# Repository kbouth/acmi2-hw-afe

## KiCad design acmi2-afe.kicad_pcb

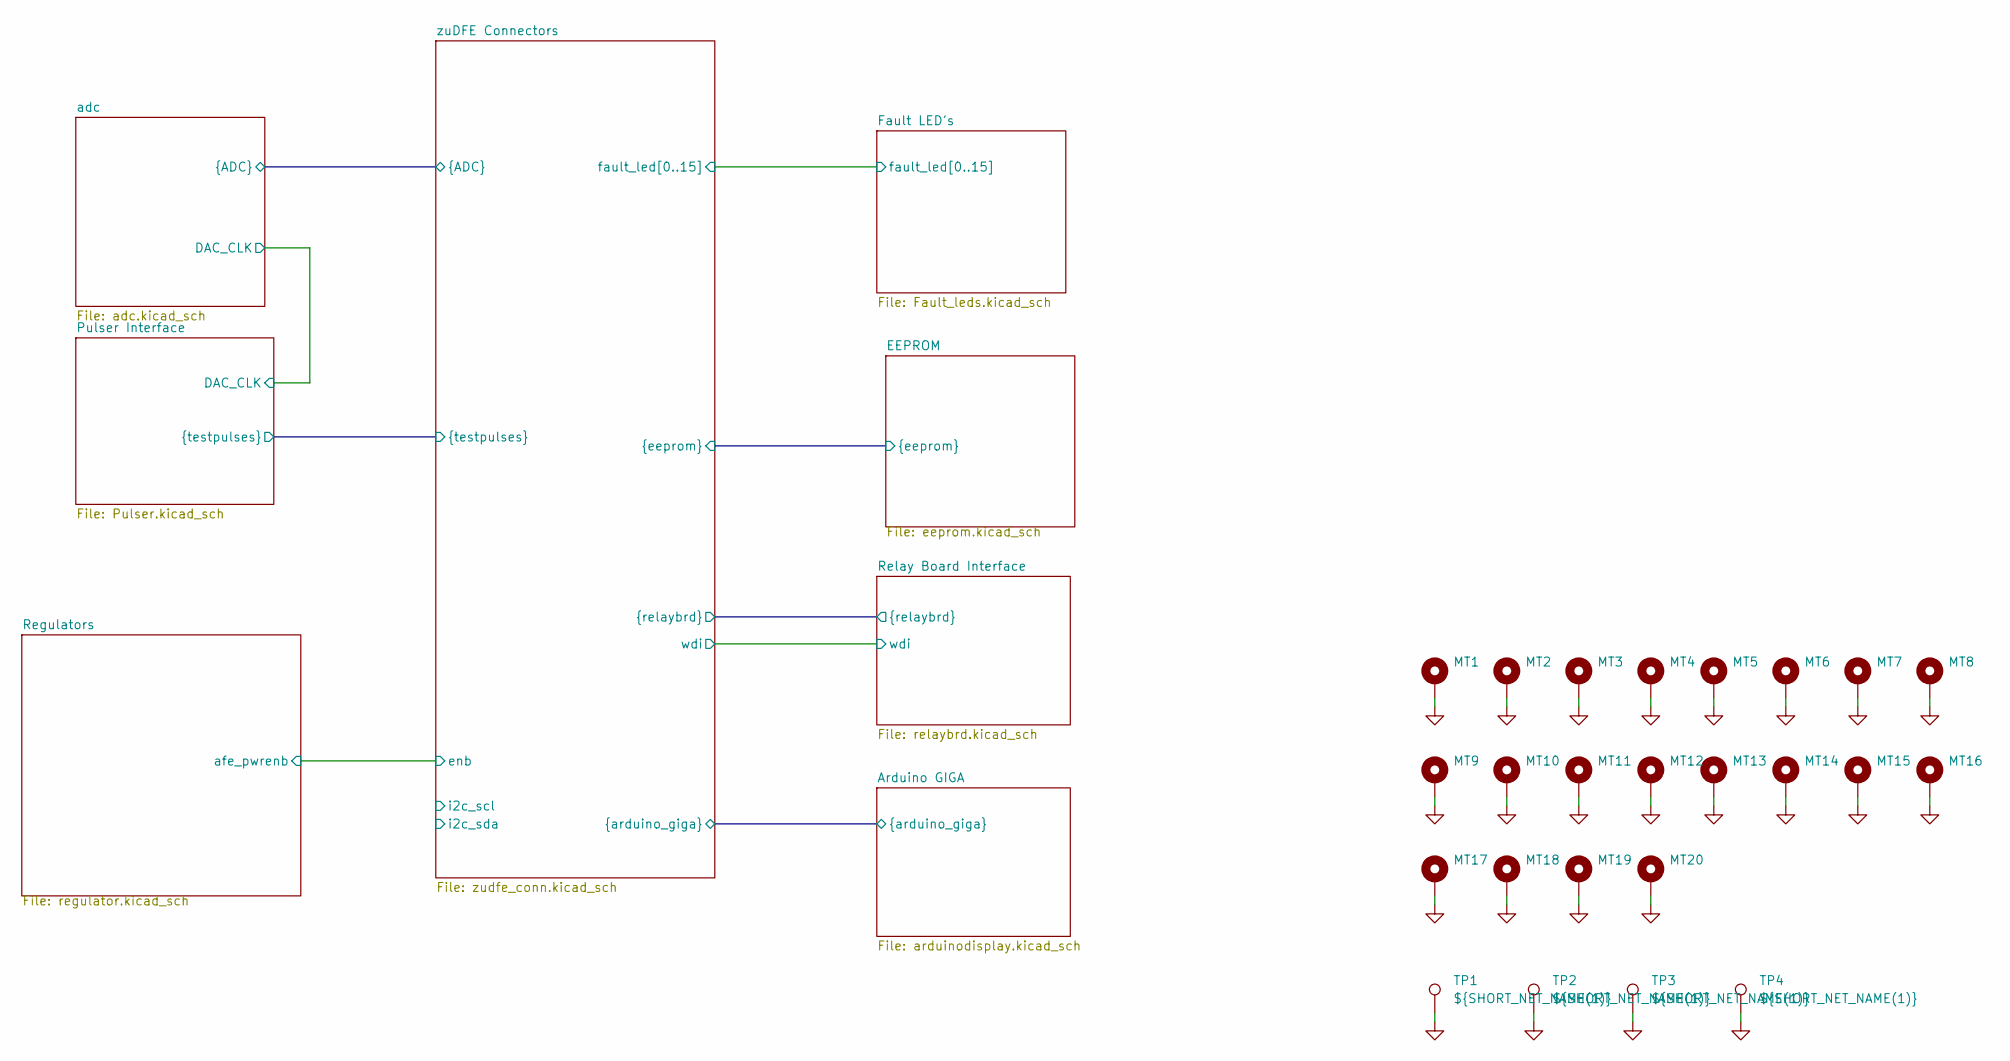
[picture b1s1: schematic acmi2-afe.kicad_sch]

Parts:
MT1, MT2, MT3, MT4, MT5, MT6, MT7, MT8: MountingHole_Pad; MountingHole_4.3mm_M4_DIN965_Pad
MT9, MT10, MT11, MT12, MT13, MT14, MT15, MT16, MT17, MT18, MT19, MT20: MountingHole_Pad; MountingHole_2.2mm_M2_DIN965_Pad
TP1, TP2, TP3, TP4: ${SHORT_NET_NAME(1)}; TestPoint_RCS-0C; MFG_PN RCS-0C

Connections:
GND: MT1.1 (1_1), MT2.1 (1_1), MT3.1 (1_1), MT4.1 (1_1), MT5.1 (1_1), MT6.1 (1_1), MT7.1 (1_1), MT8.1 (1_1), MT9.1 (1_1), MT10.1 (1_1), MT11.1 (1_1), MT12.1 (1_1), MT13.1 (1_1), MT14.1 (1_1), MT15.1 (1_1), MT16.1 (1_1), MT17.1 (1_1), MT18.1 (1_1), MT19.1 (1_1), MT20.1 (1_1), TP1.1 (1_1), TP2.1 (1_1), TP3.1 (1_1), TP4.1 (1_1); also elsewhere on the board

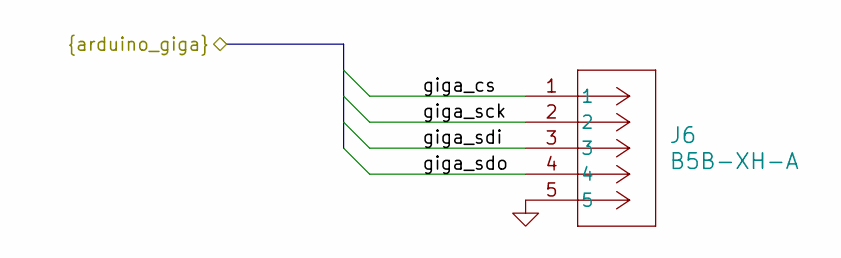
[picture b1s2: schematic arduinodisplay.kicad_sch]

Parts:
J6: B5B-XH-A; CONN_B5B-XH-A_JST

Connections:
/Arduino GIGA/giga_cs: J6.1; also elsewhere on the board
/Arduino GIGA/giga_sck: J6.2; also elsewhere on the board
/Arduino GIGA/giga_sdi: J6.3; also elsewhere on the board
/Arduino GIGA/giga_sdo: J6.4; also elsewhere on the board
GND: J6.5; also elsewhere on the board

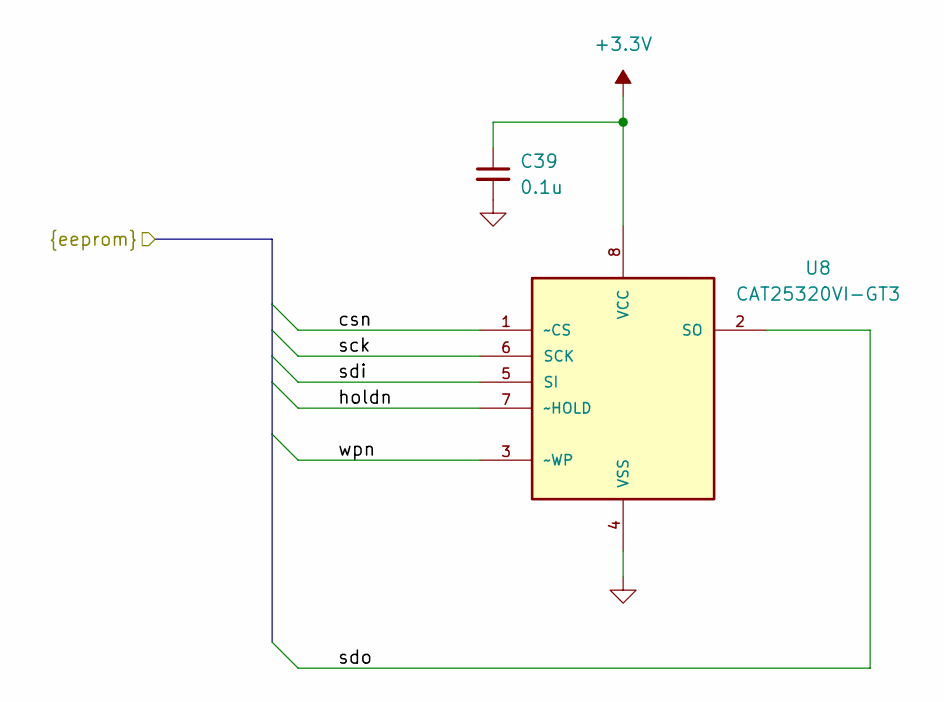
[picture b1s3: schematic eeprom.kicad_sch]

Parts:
C39: 0.1u; C_0805_2012Metric; MFG_PN TMF212B7104KGHT
U8: CAT25320VI-GT3; SOIC127P600X175-8N; MFG_PN CAT25320VI-GT3

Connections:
+3.3V: C39.1, U8.8 (VCC); also elsewhere on the board
/EEPROM/csn: U8.1 (~CS); also elsewhere on the board
/EEPROM/holdn: U8.7 (~HOLD); also elsewhere on the board
/EEPROM/sck: U8.6 (SCK); also elsewhere on the board
/EEPROM/sdi: U8.5 (SI); also elsewhere on the board
/EEPROM/sdo: U8.2 (SO); also elsewhere on the board
/EEPROM/wpn: U8.3 (~WP); also elsewhere on the board
GND: C39.2, U8.4 (VSS); also elsewhere on the board

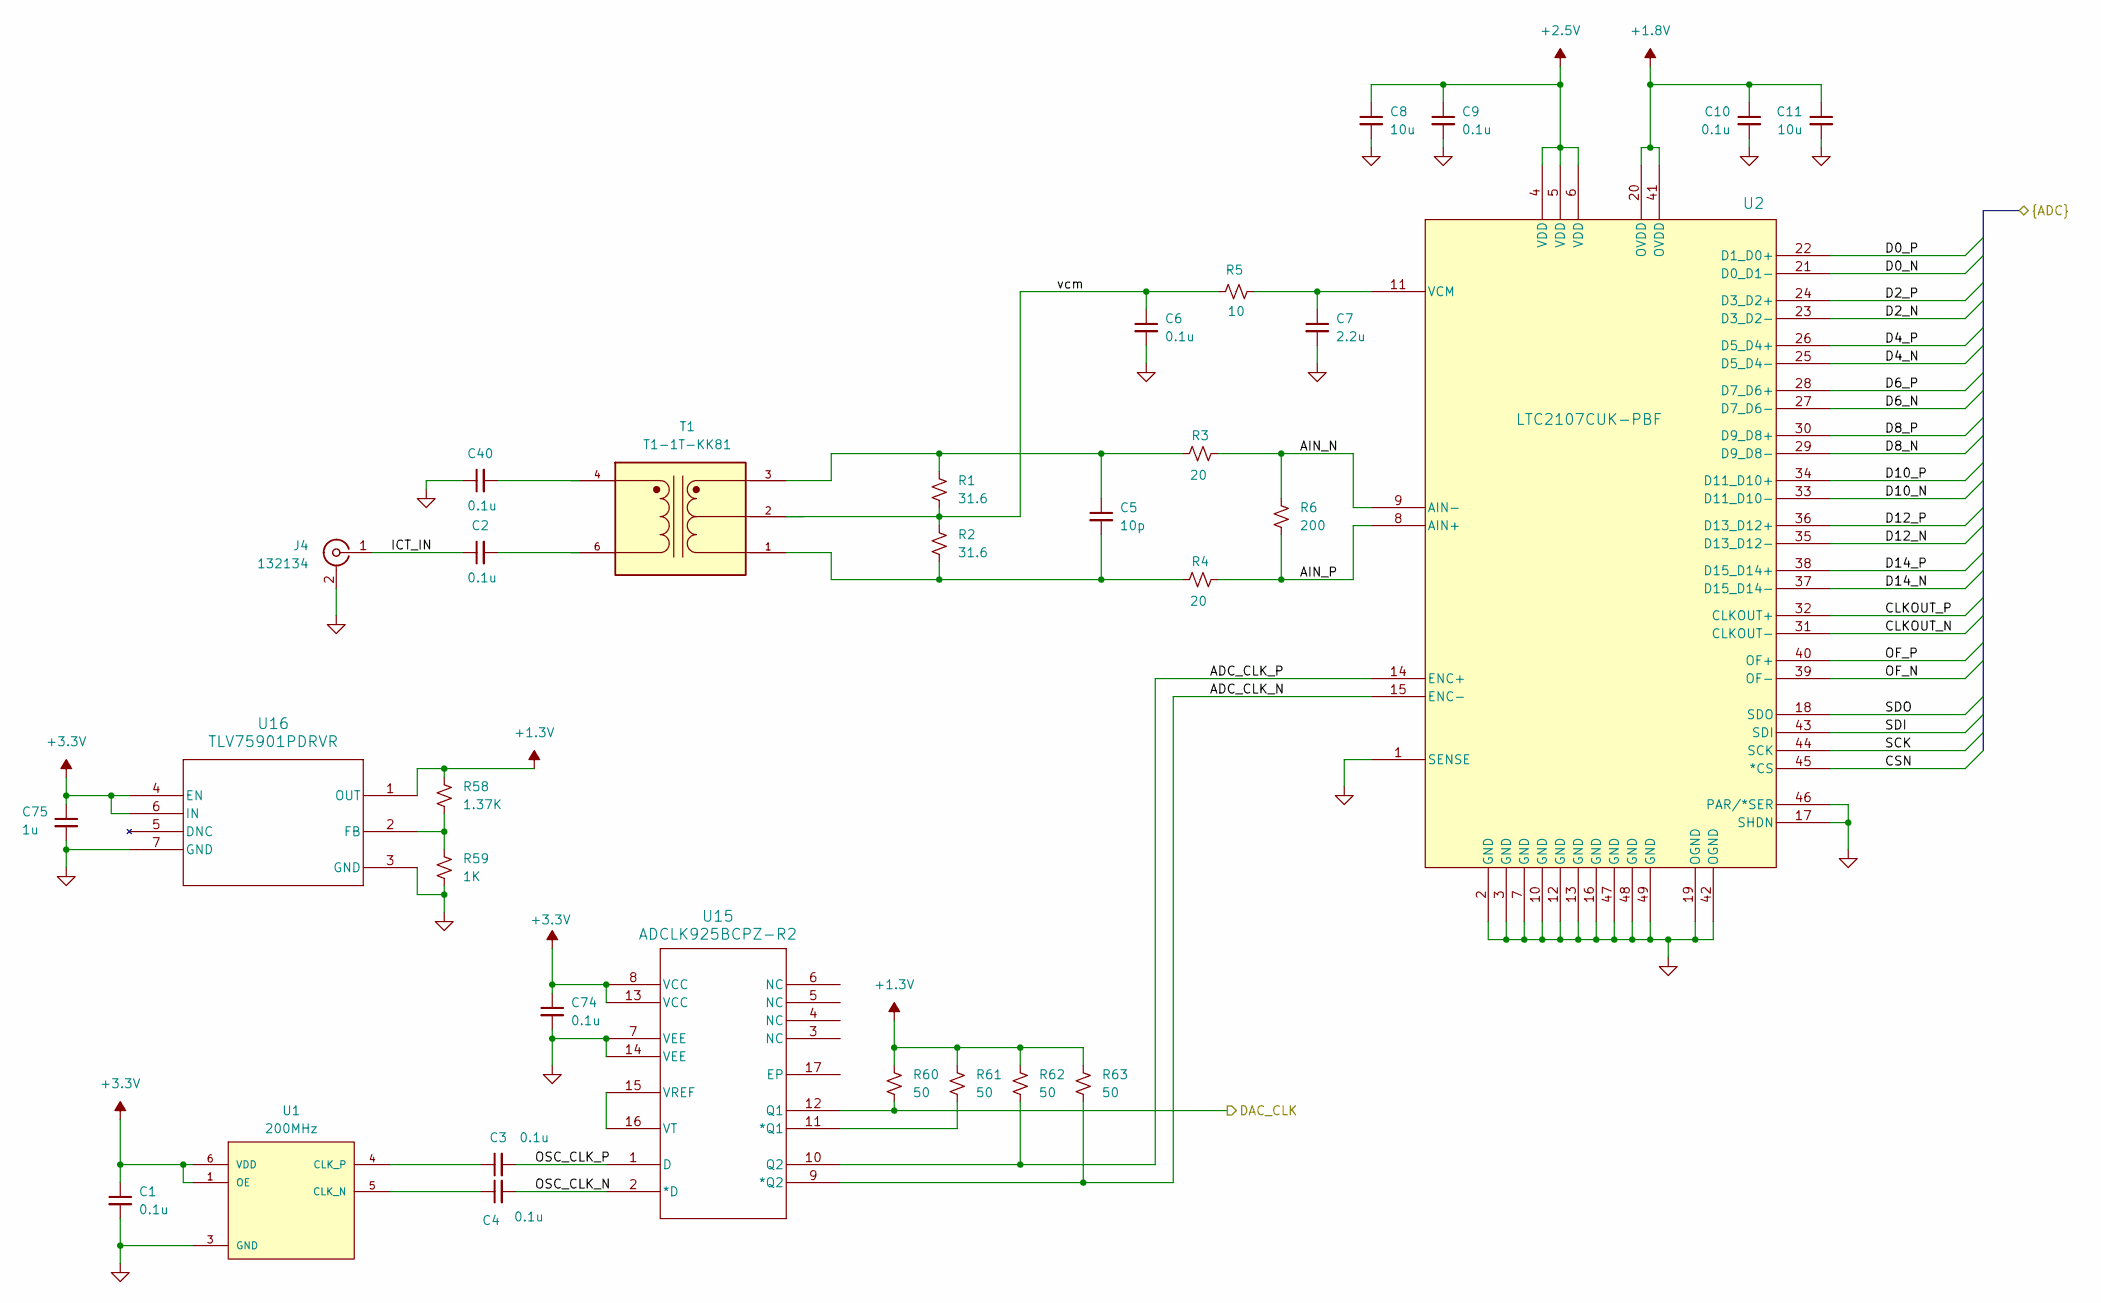
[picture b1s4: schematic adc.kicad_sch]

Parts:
C1, C2, C3, C4, C6, C9, C10, C40, C74: 0.1u; C_0805_2012Metric; MFG_PN TMF212B7104KGHT
C5: 10p; C_0805_2012Metric; MFG_PN QVS212CG100JDHT
C7: 2.2u; C_0805_2012Metric; MFG_PN UMK212BB7225KG-T
C8, C11: 10u; C_0805_2012Metric; MFG_PN GRM21BR61C106KE15K
C75: 1u; C_0805_2012Metric; MFG_PN TMF212B7104KGHT
J4: 132134; SMA_Amphenol_132134_Vertical; MFG_PN 132134
R1, R2: 31.6; R_0805_2012Metric; MFG_PN ERJ-6ENF31R6V
R3, R4: 20; R_0805_2012Metric; MFG_PN ERJ-6ENF20R0V
R5: 10; R_0805_2012Metric; MFG_PN ERJ-6ENF10R0V
R6: 200; R_0805_2012Metric; MFG_PN ERJ-6ENF2000V
R58: 1.37K; R_0805_2012Metric; MFG_PN ERJ-6ENF31R6V
R59: 1K; R_0805_2012Metric; MFG_PN ERJ-6ENF31R6V
R60, R61, R62, R63: 50; R_0805_2012Metric; MFG_PN ERJ-6ENF31R6V
T1: T1-1T-KK81; XFMR_T1-1T-KK81_; PARTREV B
U1: 200MHz; OSC_ECS-LVDS33-2000-BN; MFG_PN ECS-LVDS33-2000-BN
U2: LTC2107CUK-PBF; QFN-48_UK_LIT; MFG_PN LTC2107CUK#PBF
U15: ADCLK925BCPZ-R2; CP_16_3_ADI
U16: TLV75901PDRVR; WSON6_DRV_TEX

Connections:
+1.3V: R58.1, R60.1, R61.1, R62.1, R63.1, U16.1 (OUT)
+1.8V: C10.1, C11.1, U2.20 (OVDD), U2.41 (OVDD); also elsewhere on the board
+2.5V: C8.1, C9.1, U2.4 (VDD), U2.5 (VDD), U2.6 (VDD); also elsewhere on the board
+3.3V: C1.1, C74.1, C75.1, U1.1 (OE), U1.6 (VDD), U15.8 (VCC), U15.13 (VCC), U16.4 (EN), U16.6 (IN); also elsewhere on the board
/Pulser Interface/DAC_CLK: R60.2, U15.12 (Q1); also elsewhere on the board
/adc/ADC_CLK_N: R63.2, U2.15 (ENC-), U15.9 (*Q2)
/adc/ADC_CLK_P: R62.2, U2.14 (ENC+), U15.10 (Q2)
/adc/AIN_N: R3.1, R6.1, U2.9 (AIN-)
/adc/AIN_P: R4.1, R6.2, U2.8 (AIN+)
/adc/CLKOUT_N: U2.31 (CLKOUT-); also elsewhere on the board
/adc/CLKOUT_P: U2.32 (CLKOUT+); also elsewhere on the board
/adc/CSN: U2.45 (*CS); also elsewhere on the board
/adc/D0_N: U2.21 (D0_D1-); also elsewhere on the board
/adc/D0_P: U2.22 (D1_D0+); also elsewhere on the board
/adc/D2_N: U2.23 (D3_D2-); also elsewhere on the board
/adc/D2_P: U2.24 (D3_D2+); also elsewhere on the board
/adc/D4_N: U2.25 (D5_D4-); also elsewhere on the board
/adc/D4_P: U2.26 (D5_D4+); also elsewhere on the board
/adc/D6_N: U2.27 (D7_D6-); also elsewhere on the board
/adc/D6_P: U2.28 (D7_D6+); also elsewhere on the board
/adc/D8_N: U2.29 (D9_D8-); also elsewhere on the board
/adc/D8_P: U2.30 (D9_D8+); also elsewhere on the board
/adc/D10_N: U2.33 (D11_D10-); also elsewhere on the board
/adc/D10_P: U2.34 (D11_D10+); also elsewhere on the board
/adc/D12_N: U2.35 (D13_D12-); also elsewhere on the board
/adc/D12_P: U2.36 (D13_D12+); also elsewhere on the board
/adc/D14_N: U2.37 (D15_D14-); also elsewhere on the board
/adc/D14_P: U2.38 (D15_D14+); also elsewhere on the board
/adc/ICT_IN: C2.1, J4.1 (In)
/adc/OF_N: U2.39 (OF-); also elsewhere on the board
/adc/OF_P: U2.40 (OF+); also elsewhere on the board
/adc/OSC_CLK_N: C4.2, U15.2 (*D)
/adc/OSC_CLK_P: C3.2, U15.1 (D)
/adc/SCK: U2.44 (SCK); also elsewhere on the board
/adc/SDI: U2.43 (SDI); also elsewhere on the board
/adc/SDO: U2.18 (SDO); also elsewhere on the board
/adc/vcm: C6.1, R1.2, R2.1, R5.2, T1.2
GND: C1.2, C6.2, C7.2, C8.2, C9.2, C10.2, C11.2, C40.1, C74.2, C75.2, J4.2 (Ext), R59.2, U1.3 (GND), U2.1 (SENSE), U2.2 (GND), U2.3 (GND), U2.7 (GND), U2.10 (GND), U2.12 (GND), U2.13 (GND), U2.16 (GND), U2.17 (SHDN), U2.19 (OGND), U2.42 (OGND), U2.46 (PAR/*SER), U2.47 (GND), U2.48 (GND), U2.49 (GND), U15.7 (VEE), U15.14 (VEE), U16.3 (GND), U16.7 (GND); also elsewhere on the board
unnamed: C2.2, T1.6
unnamed: C5.1, R1.1, R3.2, T1.3
unnamed: C5.2, R2.2, R4.2, T1.1
unnamed: C40.2, T1.4
unnamed: C4.1, U1.5 (CLK_N)
unnamed: C3.1, U1.4 (CLK_P)
unnamed: C7.1, R5.1, U2.11 (VCM)
unnamed: R61.2, U15.11 (*Q1)
unnamed: U15.15 (VREF), U15.16 (VT)
unnamed: R58.2, R59.1, U16.2 (FB)

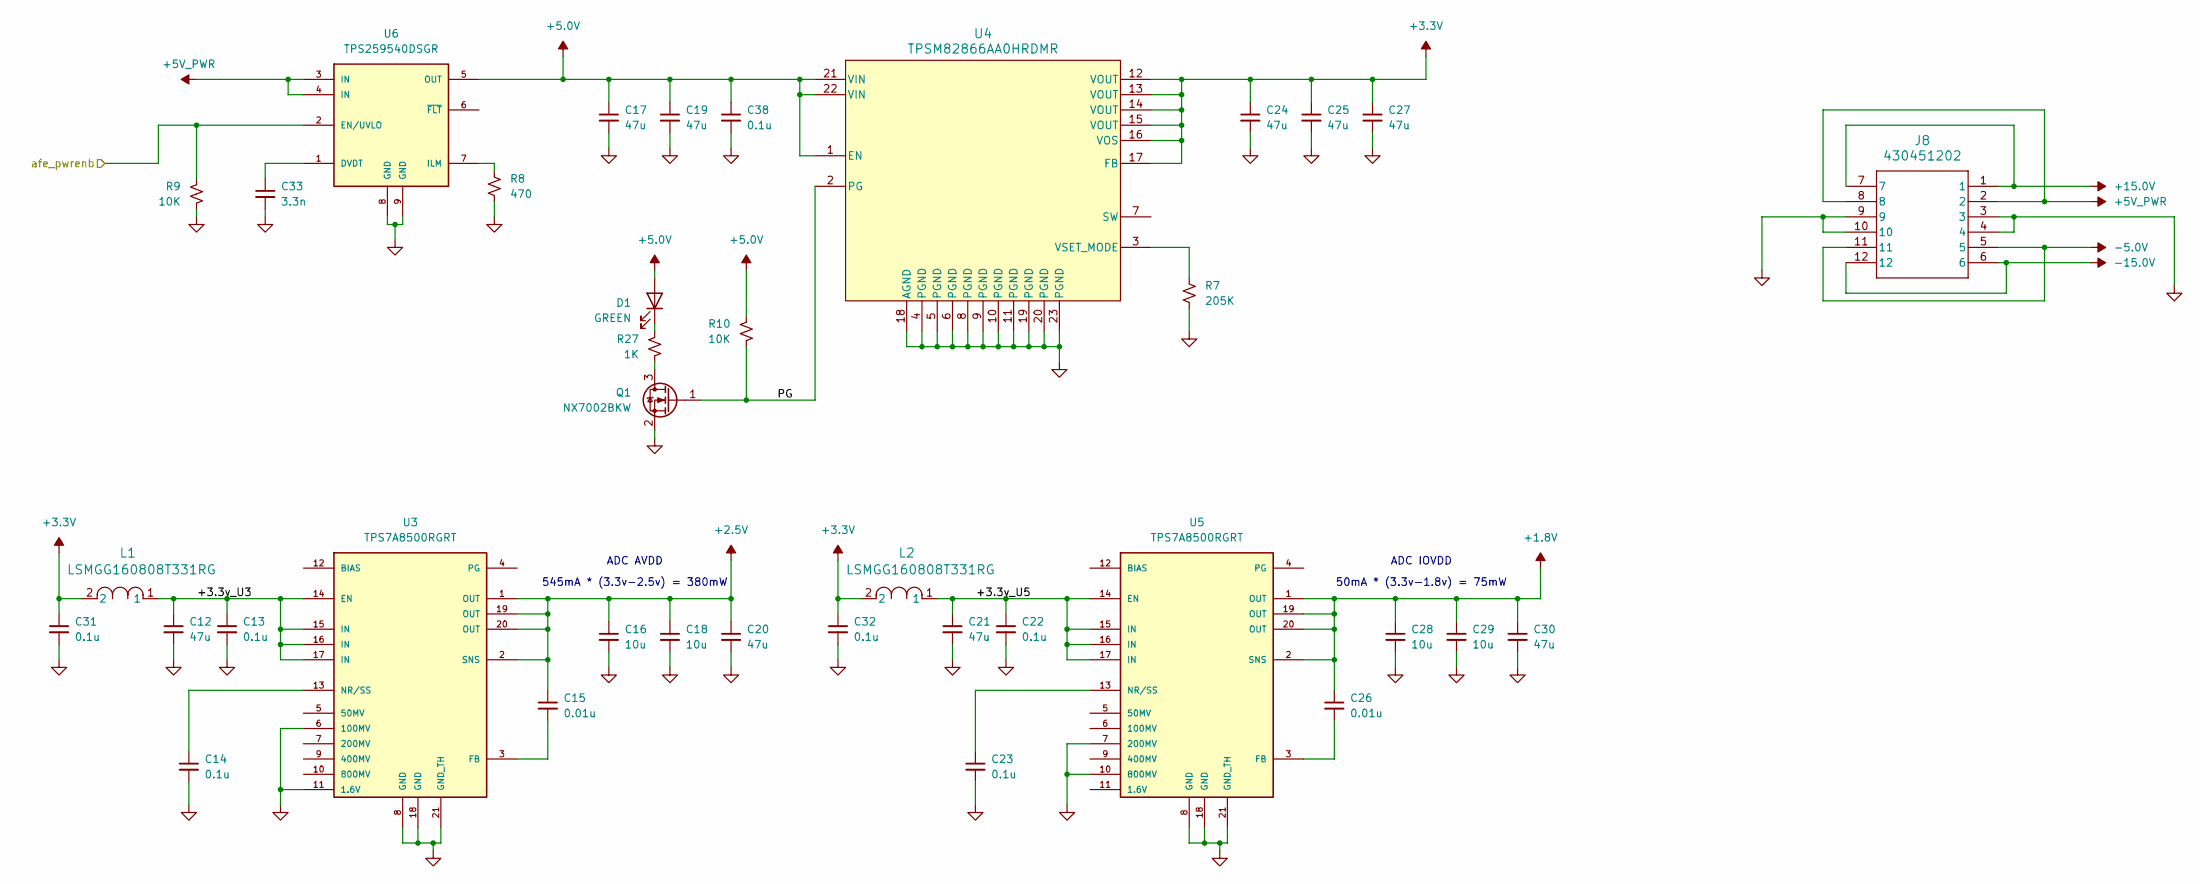
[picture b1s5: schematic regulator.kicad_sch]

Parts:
C12, C17, C19, C20, C21, C24, C25, C27, C30: 47u; C_0805_2012Metric; MFG_PN C2012X5R1A476M125AC
C13, C14, C22, C23, C31, C32, C38: 0.1u; C_0805_2012Metric; MFG_PN TMF212B7104KGHT
C15, C26: 0.01u; C_0805_2012Metric; MFG_PN MAASU21GSL8103MTNA01
C16, C18, C28, C29: 10u; C_0805_2012Metric; MFG_PN GRM21BR61C106KE15K
C33: 3.3n; C_0805_2012Metric; MFG_PN C0805X332K5RECTU
D1: GREEN; LED_0805_2012Metric; MFG_PN LTST-C191KGKT
J8: 430451202; CONN_SD-43045-001_12_MOL
L1, L2: LSMGG160808T331RG; IND_LSMG_160808_TAY; MFG_PN LSMGG160808T331RG
Q1: NX7002BKW; SOT-323_SC-70; MFG_PN NX7002BKWX
R7: 205K; R_0805_2012Metric; MFG_PN ERJ-6ENF2053V
R8: 470; R_0805_2012Metric; MFG_PN ERJ-6ENF4700V
R9, R10: 10K; R_0805_2012Metric; MFG_PN ERJ-2RKF1001X
R27: 1K; R_0805_2012Metric; MFG_PN ERJ-P06F1001V
U3, U5: TPS7A8500RGRT; QFN50P350X350X100-21N; MFG_PN TPS7A8500RGRT
U4: TPSM82866AA0HRDMR; RDM0023A-MFG; MFG_PN TPSM82866AA0HRDMR
U6: TPS259540DSGR; SON50P200X200X80-9N; MFG_PN TPS259540DSGR

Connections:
+1.8V: C26.1, C28.1, C29.1, C30.1, U5.1 (OUT), U5.2 (SNS), U5.19 (OUT), U5.20 (OUT); also elsewhere on the board
+2.5V: C15.1, C16.1, C18.1, C20.1, U3.1 (OUT), U3.2 (SNS), U3.19 (OUT), U3.20 (OUT); also elsewhere on the board
+3.3V: C24.1, C25.1, C27.1, C31.1, C32.1, L1.2, L2.2, U4.12 (VOUT), U4.13 (VOUT), U4.14 (VOUT), U4.15 (VOUT), U4.16 (VOS), U4.17 (FB); also elsewhere on the board
+5.0V: C17.1, C19.1, C38.1, D1.2 (A), R10.1, U4.1 (EN), U4.21 (VIN), U4.22 (VIN), U6.5 (OUT); also elsewhere on the board
+5V_PWR: J8.2, J8.8, U6.3 (IN), U6.4 (IN); also elsewhere on the board
+15.0V: J8.1, J8.7; also elsewhere on the board
-5.0V: J8.5, J8.11; also elsewhere on the board
-15.0V: J8.6, J8.12; also elsewhere on the board
/Regulators/+3.3v_U3: C12.1, C13.1, L1.1, U3.14 (EN), U3.15 (IN), U3.16 (IN), U3.17 (IN)
/Regulators/+3.3v_U5: C21.1, C22.1, L2.1, U5.14 (EN), U5.15 (IN), U5.16 (IN), U5.17 (IN)
/Regulators/PG: Q1.1 (G), R10.2, U4.2 (PG)
/Regulators/afe_pwrenb: R9.1, U6.2 (EN/UVLO); also elsewhere on the board
GND: C12.2, C13.2, C14.2, C16.2, C17.2, C18.2, C19.2, C20.2, C21.2, C22.2, C23.2, C24.2, C25.2, C27.2, C28.2, C29.2, C30.2, C31.2, C32.2, C33.2, C38.2, J8.3, J8.4, J8.9, J8.10, Q1.2 (S), R7.2, R8.2, R9.2, U3.6 (100MV), U3.8 (GND), U3.11 (1.6V), U3.18 (GND), U3.21 (GND_TH), U4.4 (PGND), U4.5 (PGND), U4.6 (PGND), U4.8 (PGND), U4.9 (PGND), U4.10 (PGND), U4.11 (PGND), U4.18 (AGND), U4.19 (PGND), U4.20 (PGND), U4.23 (PGND), U5.7 (200MV), U5.8 (GND), U5.10 (800MV), U5.18 (GND), U5.21 (GND_TH), U6.8 (GND), U6.9 (GND); also elsewhere on the board
unnamed: D1.1 (K), R27.1
unnamed: Q1.3 (D), R27.2
unnamed: C15.2, U3.3 (FB)
unnamed: C14.1, U3.13 (NR/SS)
unnamed: R7.1, U4.3 (VSET_MODE)
unnamed: C26.2, U5.3 (FB)
unnamed: C23.1, U5.13 (NR/SS)
unnamed: C33.1, U6.1 (DVDT)
unnamed: R8.1, U6.7 (ILM)

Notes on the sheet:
50mA * (3.3v-1.8v) = 75mW
ADC IOVDD
ADC AVDD
545mA * (3.3v-2.5v) = 380mW

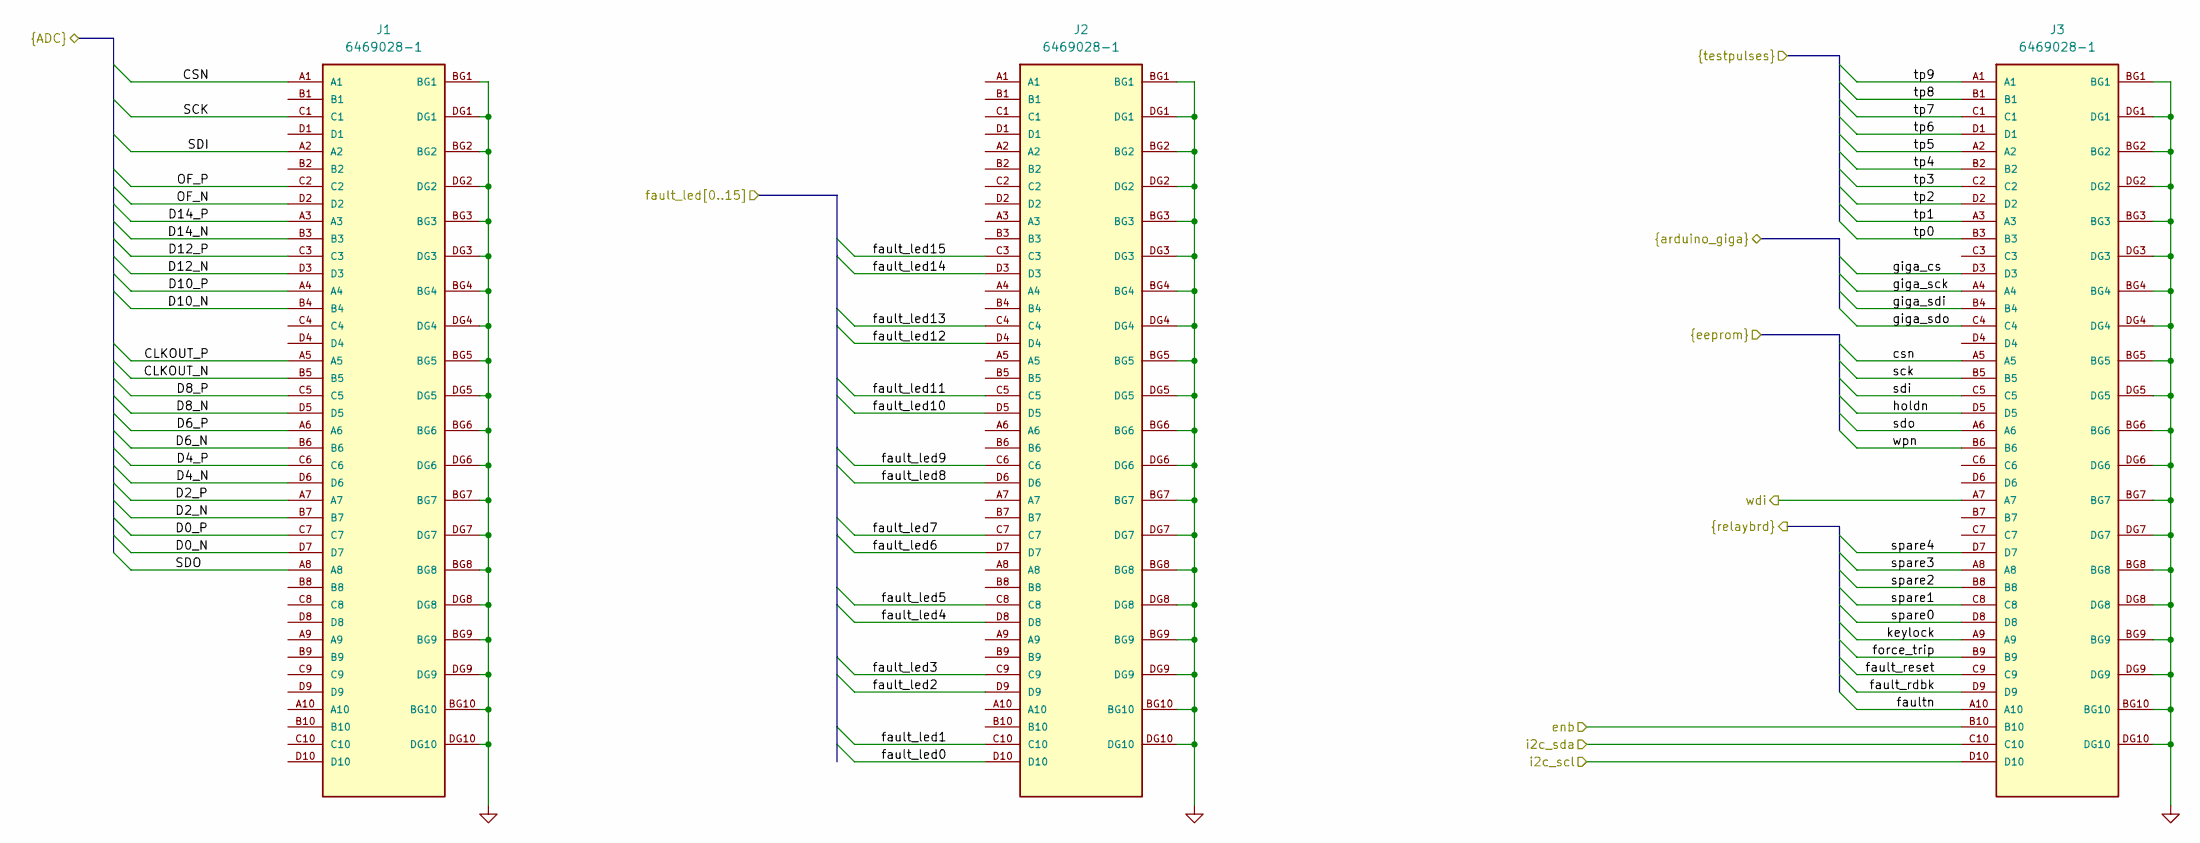
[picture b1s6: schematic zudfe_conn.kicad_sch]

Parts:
J1, J2, J3: 6469028-1; TE_6469028-1; PARTREV E

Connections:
/Arduino GIGA/giga_cs: J3.D3; also elsewhere on the board
/Arduino GIGA/giga_sck: J3.A4; also elsewhere on the board
/Arduino GIGA/giga_sdi: J3.B4; also elsewhere on the board
/Arduino GIGA/giga_sdo: J3.C4; also elsewhere on the board
/EEPROM/csn: J3.A5; also elsewhere on the board
/EEPROM/holdn: J3.D5; also elsewhere on the board
/EEPROM/sck: J3.B5; also elsewhere on the board
/EEPROM/sdi: J3.C5; also elsewhere on the board
/EEPROM/sdo: J3.A6; also elsewhere on the board
/EEPROM/wpn: J3.B6; also elsewhere on the board
/Fault LED's/fault_led0: J2.D10; also elsewhere on the board
/Fault LED's/fault_led1: J2.C10; also elsewhere on the board
/Fault LED's/fault_led2: J2.D9; also elsewhere on the board
/Fault LED's/fault_led3: J2.C9; also elsewhere on the board
/Fault LED's/fault_led4: J2.D8; also elsewhere on the board
/Fault LED's/fault_led5: J2.C8; also elsewhere on the board
/Fault LED's/fault_led6: J2.D7; also elsewhere on the board
/Fault LED's/fault_led7: J2.C7; also elsewhere on the board
/Fault LED's/fault_led8: J2.D6; also elsewhere on the board
/Fault LED's/fault_led9: J2.C6; also elsewhere on the board
/Fault LED's/fault_led10: J2.D5; also elsewhere on the board
/Fault LED's/fault_led11: J2.C5; also elsewhere on the board
/Fault LED's/fault_led12: J2.D4; also elsewhere on the board
/Fault LED's/fault_led13: J2.C4; also elsewhere on the board
/Fault LED's/fault_led14: J2.D3; also elsewhere on the board
/Fault LED's/fault_led15: J2.C3; also elsewhere on the board
/Pulser Interface/tp0: J3.B3; also elsewhere on the board
/Pulser Interface/tp1: J3.A3; also elsewhere on the board
/Pulser Interface/tp2: J3.D2; also elsewhere on the board
/Pulser Interface/tp3: J3.C2; also elsewhere on the board
/Pulser Interface/tp4: J3.B2; also elsewhere on the board
/Pulser Interface/tp5: J3.A2; also elsewhere on the board
/Pulser Interface/tp6: J3.D1; also elsewhere on the board
/Pulser Interface/tp7: J3.C1; also elsewhere on the board
/Pulser Interface/tp8: J3.B1; also elsewhere on the board
/Pulser Interface/tp9: J3.A1; also elsewhere on the board
/Regulators/afe_pwrenb: J3.B10; also elsewhere on the board
/Relay Board Interface/fault_rdbk: J3.D9; also elsewhere on the board
/Relay Board Interface/fault_reset: J3.C9; also elsewhere on the board
/Relay Board Interface/faultn: J3.A10; also elsewhere on the board
/Relay Board Interface/force_trip: J3.B9; also elsewhere on the board
/Relay Board Interface/keylock: J3.A9; also elsewhere on the board
/Relay Board Interface/spare0: J3.D8; also elsewhere on the board
/Relay Board Interface/spare1: J3.C8; also elsewhere on the board
/Relay Board Interface/spare2: J3.B8; also elsewhere on the board
/Relay Board Interface/spare3: J3.A8; also elsewhere on the board
/Relay Board Interface/spare4: J3.D7; also elsewhere on the board
/Relay Board Interface/wdi: J3.A7; also elsewhere on the board
/adc/CLKOUT_N: J1.B5; also elsewhere on the board
/adc/CLKOUT_P: J1.A5; also elsewhere on the board
/adc/CSN: J1.A1; also elsewhere on the board
/adc/D0_N: J1.D7; also elsewhere on the board
/adc/D0_P: J1.C7; also elsewhere on the board
/adc/D2_N: J1.B7; also elsewhere on the board
/adc/D2_P: J1.A7; also elsewhere on the board
/adc/D4_N: J1.D6; also elsewhere on the board
/adc/D4_P: J1.C6; also elsewhere on the board
/adc/D6_N: J1.B6; also elsewhere on the board
/adc/D6_P: J1.A6; also elsewhere on the board
/adc/D8_N: J1.D5; also elsewhere on the board
/adc/D8_P: J1.C5; also elsewhere on the board
/adc/D10_N: J1.B4; also elsewhere on the board
/adc/D10_P: J1.A4; also elsewhere on the board
/adc/D12_N: J1.D3; also elsewhere on the board
/adc/D12_P: J1.C3; also elsewhere on the board
/adc/D14_N: J1.B3; also elsewhere on the board
/adc/D14_P: J1.A3; also elsewhere on the board
/adc/OF_N: J1.D2; also elsewhere on the board
/adc/OF_P: J1.C2; also elsewhere on the board
/adc/SCK: J1.C1; also elsewhere on the board
/adc/SDI: J1.A2; also elsewhere on the board
/adc/SDO: J1.A8; also elsewhere on the board
/zuDFE Connectors/i2c_scl: J3.D10
/zuDFE Connectors/i2c_sda: J3.C10
GND: J1.BG1, J1.BG2, J1.BG3, J1.BG4, J1.BG5, J1.BG6, J1.BG7, J1.BG8, J1.BG9, J1.BG10, J1.DG1, J1.DG2, J1.DG3, J1.DG4, J1.DG5, J1.DG6, J1.DG7, J1.DG8, J1.DG9, J1.DG10, J2.BG1, J2.BG2, J2.BG3, J2.BG4, J2.BG5, J2.BG6, J2.BG7, J2.BG8, J2.BG9, J2.BG10, J2.DG1, J2.DG2, J2.DG3, J2.DG4, J2.DG5, J2.DG6, J2.DG7, J2.DG8, J2.DG9, J2.DG10, J3.BG1, J3.BG2, J3.BG3, J3.BG4, J3.BG5, J3.BG6, J3.BG7, J3.BG8, J3.BG9, J3.BG10, J3.DG1, J3.DG2, J3.DG3, J3.DG4, J3.DG5, J3.DG6, J3.DG7, J3.DG8, J3.DG9, J3.DG10; also elsewhere on the board

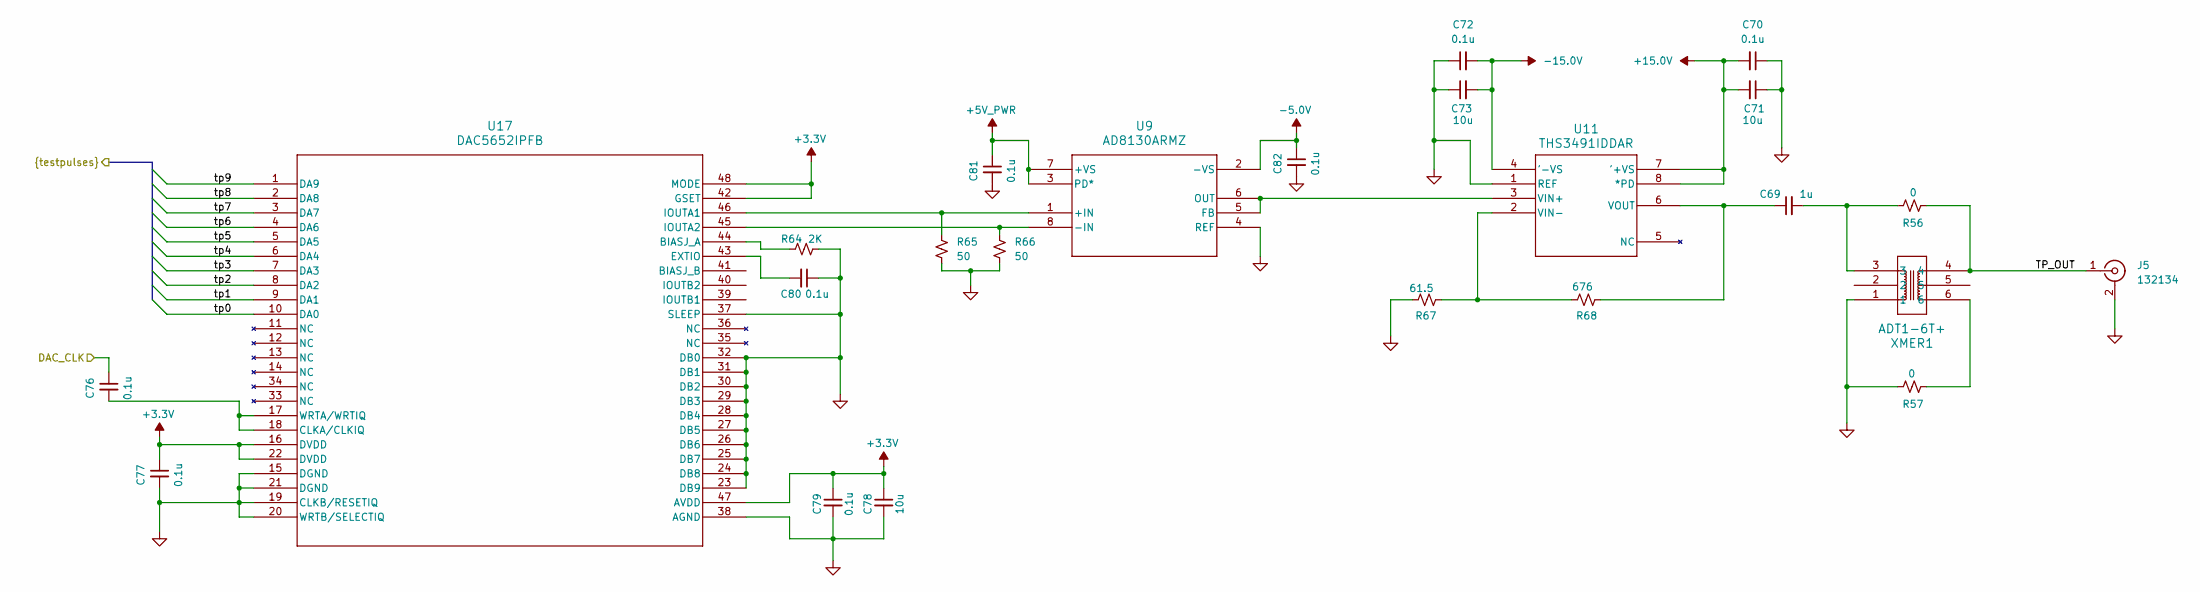
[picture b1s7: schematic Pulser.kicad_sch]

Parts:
C69: 1u; C_0805_2012Metric; MFG_PN TMF212B7104KGHT
C70, C72, C76, C77, C79, C80, C81, C82: 0.1u; C_0805_2012Metric; MFG_PN TMF212B7104KGHT
C71, C73: 10u; C_1206_3216Metric; MFG_PN TMF212B7104KGHT
C78: 10u; C_0805_2012Metric; MFG_PN TMF212B7104KGHT
J5: 132134; SMA_Amphenol_132134_Vertical; MFG_PN 132134
R56, R57: 0; R_0805_2012Metric; MFG_PN ERJ-6ENF31R6V
R64: 2K; R_0805_2012Metric; MFG_PN ERJ-6ENF31R6V
R65, R66: 50; R_0805_2012Metric; MFG_PN ERJ-6ENF31R6V
R67: 61.5; R_0805_2012Metric; MFG_PN ERJ-6ENF31R6V
R68: 676; R_0805_2012Metric; MFG_PN ERJ-6ENF31R6V
U9: AD8130ARMZ; RM_8_ADI
U11: THS3491IDDAR; DDA8_TEX
U17: DAC5652IPFB; PFB48
XMER1: ADT1-6T+; CD637_MNC

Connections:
+3.3V: C77.1, C78.1, C79.1, U17.16 (DVDD), U17.22 (DVDD), U17.42 (GSET), U17.47 (AVDD), U17.48 (MODE); also elsewhere on the board
+5V_PWR: C81.1, U9.3 (PD*), U9.7 (+VS); also elsewhere on the board
+15.0V: C70.2, C71.2, U11.7 ('+VS), U11.8 (*PD); also elsewhere on the board
-5.0V: C82.1, U9.2 (-VS); also elsewhere on the board
-15.0V: C72.2, C73.2, U11.4 ('-VS); also elsewhere on the board
/Pulser Interface/DAC_CLK: C76.1; also elsewhere on the board
/Pulser Interface/TP_OUT: J5.1 (In), R56.1, XMER1.4
/Pulser Interface/tp0: U17.10 (DA0); also elsewhere on the board
/Pulser Interface/tp1: U17.9 (DA1); also elsewhere on the board
/Pulser Interface/tp2: U17.8 (DA2); also elsewhere on the board
/Pulser Interface/tp3: U17.7 (DA3); also elsewhere on the board
/Pulser Interface/tp4: U17.6 (DA4); also elsewhere on the board
/Pulser Interface/tp5: U17.5 (DA5); also elsewhere on the board
/Pulser Interface/tp6: U17.4 (DA6); also elsewhere on the board
/Pulser Interface/tp7: U17.3 (DA7); also elsewhere on the board
/Pulser Interface/tp8: U17.2 (DA8); also elsewhere on the board
/Pulser Interface/tp9: U17.1 (DA9); also elsewhere on the board
GND: C70.1, C71.1, C72.1, C73.1, C77.2, C78.2, C79.2, C80.1, C81.2, C82.2, J5.2 (Ext), R57.2, R64.2, R65.2, R66.2, R67.1, U9.4 (REF), U11.1 (REF), U17.15 (DGND), U17.19 (CLKB/RESETIQ), U17.20 (WRTB/SELECTIQ), U17.21 (DGND), U17.23 (DB9), U17.24 (DB8), U17.25 (DB7), U17.26 (DB6), U17.27 (DB5), U17.28 (DB4), U17.29 (DB3), U17.30 (DB2), U17.31 (DB1), U17.32 (DB0), U17.37 (SLEEP), U17.38 (AGND), XMER1.1; also elsewhere on the board
unnamed: C69.2, R56.2, XMER1.3
unnamed: R57.1, XMER1.6
unnamed: U9.5 (FB), U9.6 (OUT), U11.3 (VIN+)
unnamed: R67.2, R68.1, U11.2 (VIN-)
unnamed: C69.1, R68.2, U11.6 (VOUT)
unnamed: R64.1, U17.44 (BIASJ_A)
unnamed: C76.2, U17.17 (WRTA/WRTIQ), U17.18 (CLKA/CLKIQ)
unnamed: C80.2, U17.43 (EXTIO)
unnamed: R65.1, U9.1 (+IN), U17.46 (IOUTA1)
unnamed: R66.1, U9.8 (-IN), U17.45 (IOUTA2)
